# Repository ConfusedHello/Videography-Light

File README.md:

# LUXCRAFT - DIY Film Light

Ever wanted a videography light but died when seeing the insane prices? Me too! This project involves a DIY, high-power RGBW film light built by [@ConfusedHello](https://github.com/confusedhello) and [@Jayx2u](https://github.com/Jayx2u/) for the Hack Club [Highway to Hardware](https://highway.hackclub.com/) program!

We decided to design this project because as students, we honestly don't have the spare cash lying around for one, and we wanted a nice accent light for our planned upcoming videos. It utilises 36 *current controlled* RGBW LEDs running off a 48V supply and controlled with a Xiao RP2040!

For details about the design process or other information, check out the [development journal](https://highway.hackclub.com/projects/ConfusedHello/Videography-Light). A local copy is available in [JOURNAL.md](https://github.com/ConfusedHello/Videography-Light/blob/main/JOURNAL.md).

## The Design
Here's a quick diagram showing how the project works~

And a nice rendered image of the case and control board-

As well as the schematic and PCB for both the control and light boards!

Also the CAD because apparently that's necessary.

## Bill of Materials
Also available in .csv format in [BOM.csv](https://github.com/ConfusedHello/Videography-Light/blob/main/BOM.csv)! BOMs for the PCBs are in [ControlBoard.csv](https://github.com/ConfusedHello/Videography-Light/blob/main/src/Production/Control%20PCB/ControlBoard.csv) and [VideographyLight.csv](https://github.com/ConfusedHello/Videography-Light/blob/main/src/Production/Light%20PCB/VideographyLight.csv)~

|Item                      |Qty.|Price (USD)|Ext. (USD)|Link                                                 |
|--------------------------|----|-----------|----------|-----------------------------------------------------|
|997-L1MCRGB2295MP0        |36  |$1.36      |$48.96    |https://mouser.com/c/?q=997-L1MCRGB2295MP0           |
|81-GRM32EC72A106ME5K      |11  |$0.71      |$7.85     |https://mouser.com/c/?q=81-GRM32EC72A106ME5K         |
|710-7447706101            |11  |$1.01      |$11.11    |https://mouser.com/c/?q=710-7447706101               |
|71-WSLT2010R5000FEA1      |11  |$0.57      |$6.28     |https://mouser.com/c/?q=71-WSLT2010R5000FEA1         |
|625-SS1H10-E3             |11  |$0.28      |$3.11     |https://mouser.com/c/?q=625-SS1H10-E3                |
|621-AL8862SP-13           |11  |$0.54      |$5.93     |https://mouser.com/c/?q=621-AL8862SP-13              |
|179-TB0012-508-04GR       |2   |$1.29      |$2.58     |https://mouser.com/c/?q=179-TB0012-508-04GR          |
|179-TB0012-508-02GR       |2   |$0.69      |$1.38     |https://mouser.com/c/?q=179-TB0012-508-02GR          |
|579-MCP4728-E/UN          |1   |$2.50      |$2.50     |https://mouser.com/c/?q=579-MCP4728-E/UN             |
|713-102010428             |1   |$5.40      |$5.40     |https://mouser.com/c/?q=713-102010428                |
|595-LMR51606XFQDBRQ1      |1   |$2.25      |$2.25     |https://mouser.com/c/?q=595-LMR51606XFQDBRQ1         |
|179-TS046695BK100SMT      |5   |$0.16      |$0.80     |https://mouser.com/c/?q=179-TS046695BK100SMT         |
|71-CRCW12104K70JNAIF      |2   |$0.58      |$1.16     |https://mouser.com/c/?q=71-CRCW12104K70JNAIF         |
|71-CRMA1210AF100KFKF      |1   |$0.85      |$0.85     |https://mouser.com/c/?q=71-CRMA1210AF100KFKF         |
|71-CRCW0402-19.1K-E3      |1   |$0.10      |$0.10     |https://mouser.com/c/?q=71-CRCW0402-19.1K-E3         |
|71-CRCW0402-100K-E3       |1   |$0.10      |$0.10     |https://mouser.com/c/?q=71-CRCW0402-100K-E3          |
|70-IFDC5050JZER470M       |1   |$0.96      |$0.96     |https://mouser.com/c/?q=70-IFDC5050JZER470M          |
|637-1N4148W               |5   |$0.10      |$0.50     |https://mouser.com/c/?q=637-1N4148W                  |
|810-C3225X7R1H106MAC      |2   |$0.96      |$1.92     |https://mouser.com/c/?q=810-C3225X7R1H106MAC         |
|81-GRM155R71C104KA88      |2   |$0.10      |$0.20     |https://mouser.com/c/?q=81-GRM155R71C104KA88         |
|81-GRM188R72A104KA35      |1   |$0.15      |$0.15     |https://mouser.com/c/?q=81-GRM188R72A104KA35         |
|581-KAM32LR72A475KU       |1   |$0.91      |$0.91     |https://mouser.com/c/?q=581-KAM32LR72A475KU          |
|Aluminum Heatsink         |10  |$0.73      |$7.33     |https://www.aliexpress.com/item/4000723868050.html   |
|0.96 Inch OLED Display    |1   |$2.60      |$2.60     |https://www.aliexpress.com/item/1005007614149117.html|
|M2 Heat Insert            |16  |$0.11      |$1.73     |https://www.aliexpress.com/item/1005003582355741.html|
|M2 Screw (10mm)           |16  |$0.21      |$3.40     |https://www.aliexpress.com/item/1005005688616965.html|
|48V Power Supply          |1   |$25.73     |$25.73    |https://www.aliexpress.com/item/1005008528926877.html|
|JLCPCB Control Board      |1   |$2.00      |$2.00     |https://www.jlcpcb.com                               |
|JLCPCB Light Board        |1   |$2.00      |$2.00     |https://www.jlcpcb.com                               |
|JLCPCB Light Board Stencil|1   |$7.00      |$7.00     |https://www.jlcpcb.com                               |
|JLCPCB Shipping           |1   |$21.22     |$21.22    |https://www.jlcpcb.com                               |

**Total:** $178.01 USD

<hr>

Made with ❤️ by [@ConfusedHello](https://github.com/confusedhello) and [@Jayx2u](https://github.com/Jayx2u/)

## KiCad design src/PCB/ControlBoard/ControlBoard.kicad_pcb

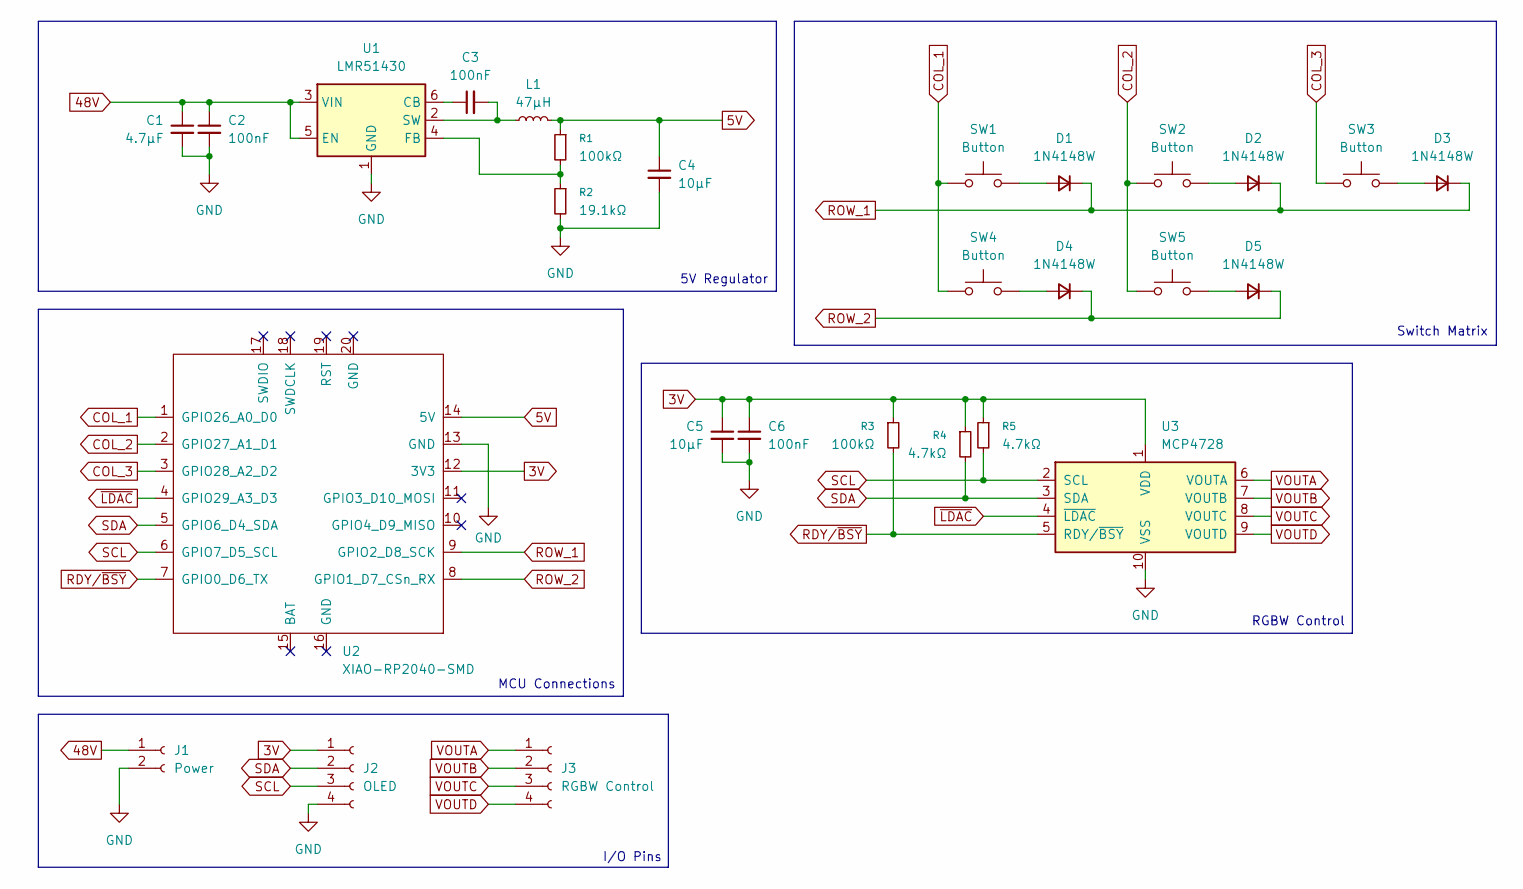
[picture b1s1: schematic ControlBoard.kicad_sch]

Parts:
C1: 4.7μF; C_1210_3225Metric_Pad1.33x2.70mm_HandSolder; Mouser 581-KAM32LR72A475KU
C2: 100nF; C_0603_1608Metric_Pad1.08x0.95mm_HandSolder; Mouser 81-GRM188R72A104KA35
C3, C6: 100nF; C_0402_1005Metric_Pad0.74x0.62mm_HandSolder; Mouser 81-GRM155R71C104KA88
C4, C5: 10μF; C_1210_3225Metric_Pad1.33x2.70mm_HandSolder; Mouser 810-C3225X7R1H106MAC
D1, D2, D3, D4, D5: 1N4148W; D_SOD-123; Mouser 637-1N4148W
J1: Power; TerminalBlock_Phoenix_MKDS-1,5-2-5.08_1x02_P5.08mm_Horizont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; Mouser 179-TB0012-508-02GR
J2: OLED; PinHeader_1x04_P1.00mm_Vertical
J3: RGBW Control; TerminalBlock_Phoenix_MKDS-1,5-4-5.08_1x04_P5.08mm_Horizont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; Mouser 179-TB0012-508-04GR
L1: 47μH; IFDC5050JZER470M; Mouser 70-IFDC5050JZER470M
R1: 100kΩ; R_0402_1005Metric_Pad0.72x0.64mm_HandSolder; Mouser 71-CRCW0402-100K-E3
R2: 19.1kΩ; R_0402_1005Metric_Pad0.72x0.64mm_HandSolder; Mouser 71-CRCW0402-19.1K-E3
R3: 100kΩ; R_1210_3225Metric_Pad1.30x2.65mm_HandSolder; Mouser 71-CRMA1210AF100KFKF
R4, R5: 4.7kΩ; R_1210_3225Metric_Pad1.30x2.65mm_HandSolder; Mouser 71-CRCW12104K70JNAIF
SW1, SW2, SW3, SW4, SW5: Button; TS046695BK100SMT; Mouser 179-TS046695BK100SMT
U1: LMR51430; SOT-23-6; Mouser 595-LMR51606XFQDBRQ1
U2: XIAO-RP2040-SMD; Mouser 713-102010428
U3: MCP4728; MSOP-10_3x3mm_P0.5mm; Mouser 579-MCP4728-E/UN

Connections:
3V: C5.1, C6.1, J2.1, R3.1, R4.1, R5.1, U2.12 (3V3), U3.1 (VDD)
5V: C4.1, L1.2, R1.1, U2.14 (5V)
48V: C1.1, C2.1, J1.1, U1.3 (VIN), U1.5 (EN)
COL_1: SW1.2 (COM_1), SW4.2 (COM_1), U2.1 (GPIO26_A0_D0)
COL_2: SW2.2 (COM_1), SW5.2 (COM_1), U2.2 (GPIO27_A1_D1)
COL_3: SW3.2 (COM_1), U2.3 (GPIO28_A2_D2)
GND: C1.2, C2.2, C4.2, C5.2, C6.2, J1.2, J2.4, R2.2, U1.1 (GND), U2.13 (GND), U3.10 (VSS)
unnamed: D1.2 (A), SW1.4 (COM_2)
unnamed: D2.2 (A), SW2.4 (COM_2)
unnamed: D3.2 (A), SW3.4 (COM_2)
unnamed: D4.2 (A), SW4.4 (COM_2)
unnamed: D5.2 (A), SW5.4 (COM_2)
unnamed: C3.1, U1.6 (CB)
unnamed: R1.2, R2.1, U1.4 (FB)
unnamed: C3.2, L1.1, U1.2 (SW)
RDY/~BSY: R3.2, U2.7 (GPIO0_D6_TX), U3.5 (RDY/~BSY)
ROW_1: D1.1 (K), D2.1 (K), D3.1 (K), U2.9 (GPIO2_D8_SCK)
ROW_2: D4.1 (K), D5.1 (K), U2.8 (GPIO1_D7_CSn_RX)
SCL: J2.3, R5.2, U2.6 (GPIO7_D5_SCL), U3.2 (SCL)
SDA: J2.2, R4.2, U2.5 (GPIO6_D4_SDA), U3.3 (SDA)
VOUTA: J3.1, U3.6 (VOUTA)
VOUTB: J3.2, U3.7 (VOUTB)
VOUTC: J3.3, U3.8 (VOUTC)
VOUTD: J3.4, U3.9 (VOUTD)
~LDAC: U2.4 (GPIO29_A3_D3), U3.4 (~LDAC)

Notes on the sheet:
RGBW Control
5V Regulator
Switch Matrix
MCU Connections
I/O Pins

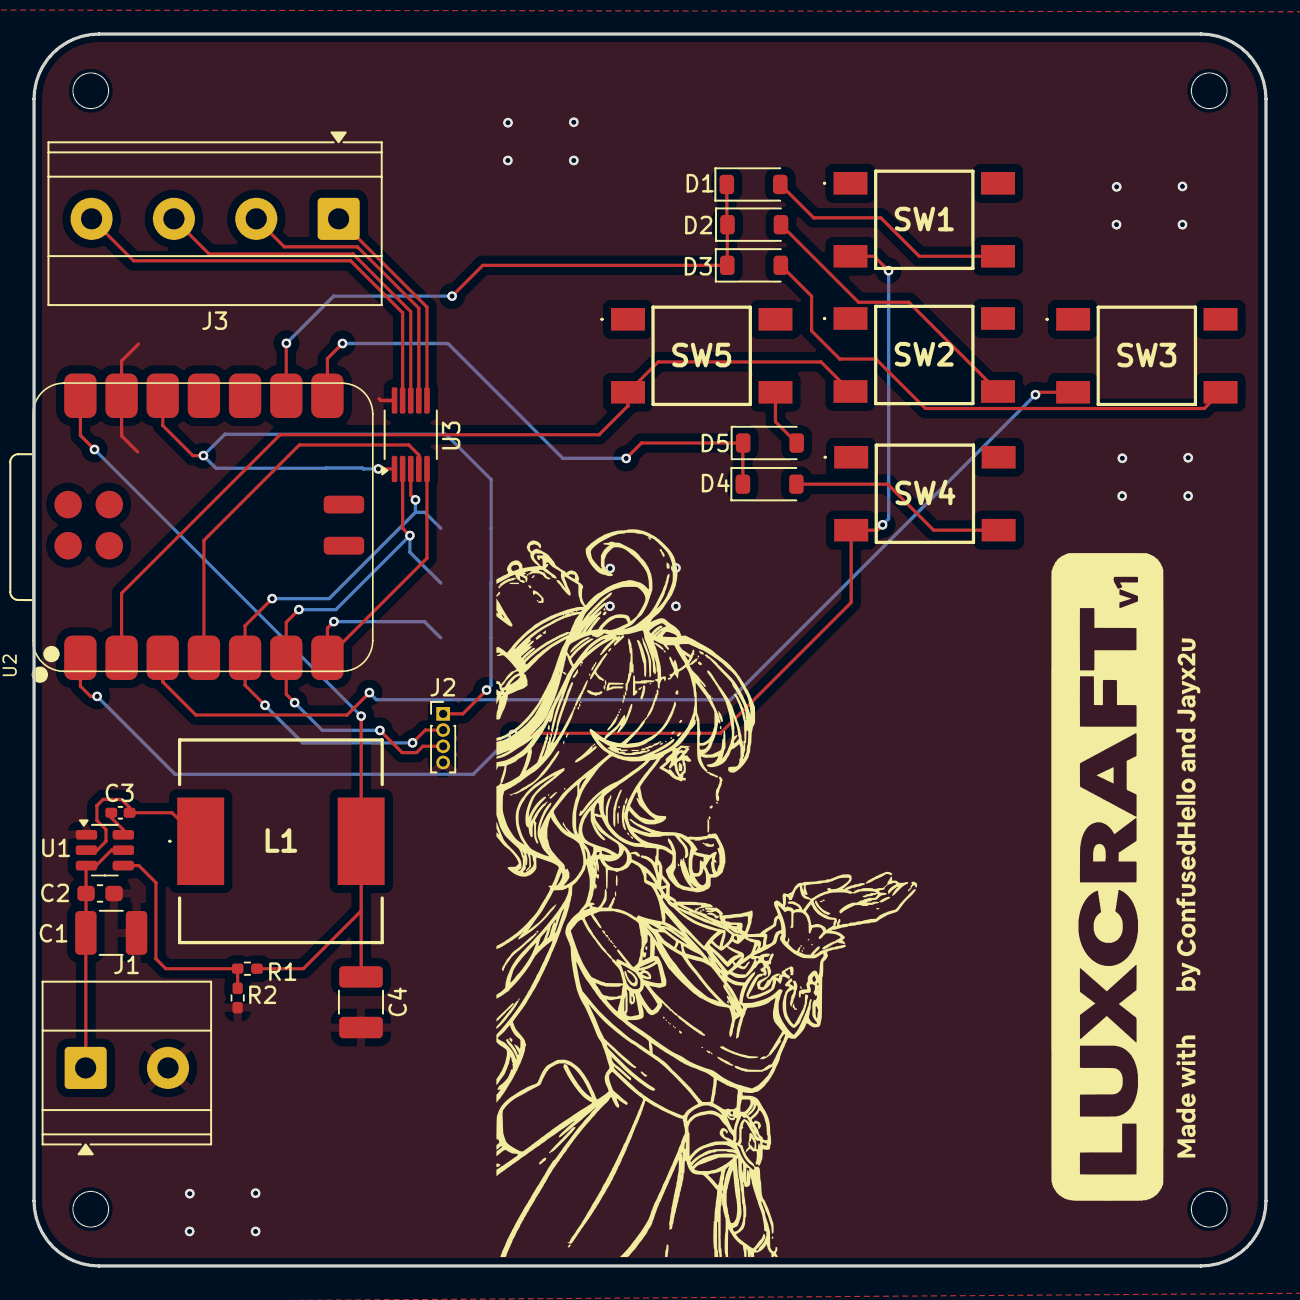
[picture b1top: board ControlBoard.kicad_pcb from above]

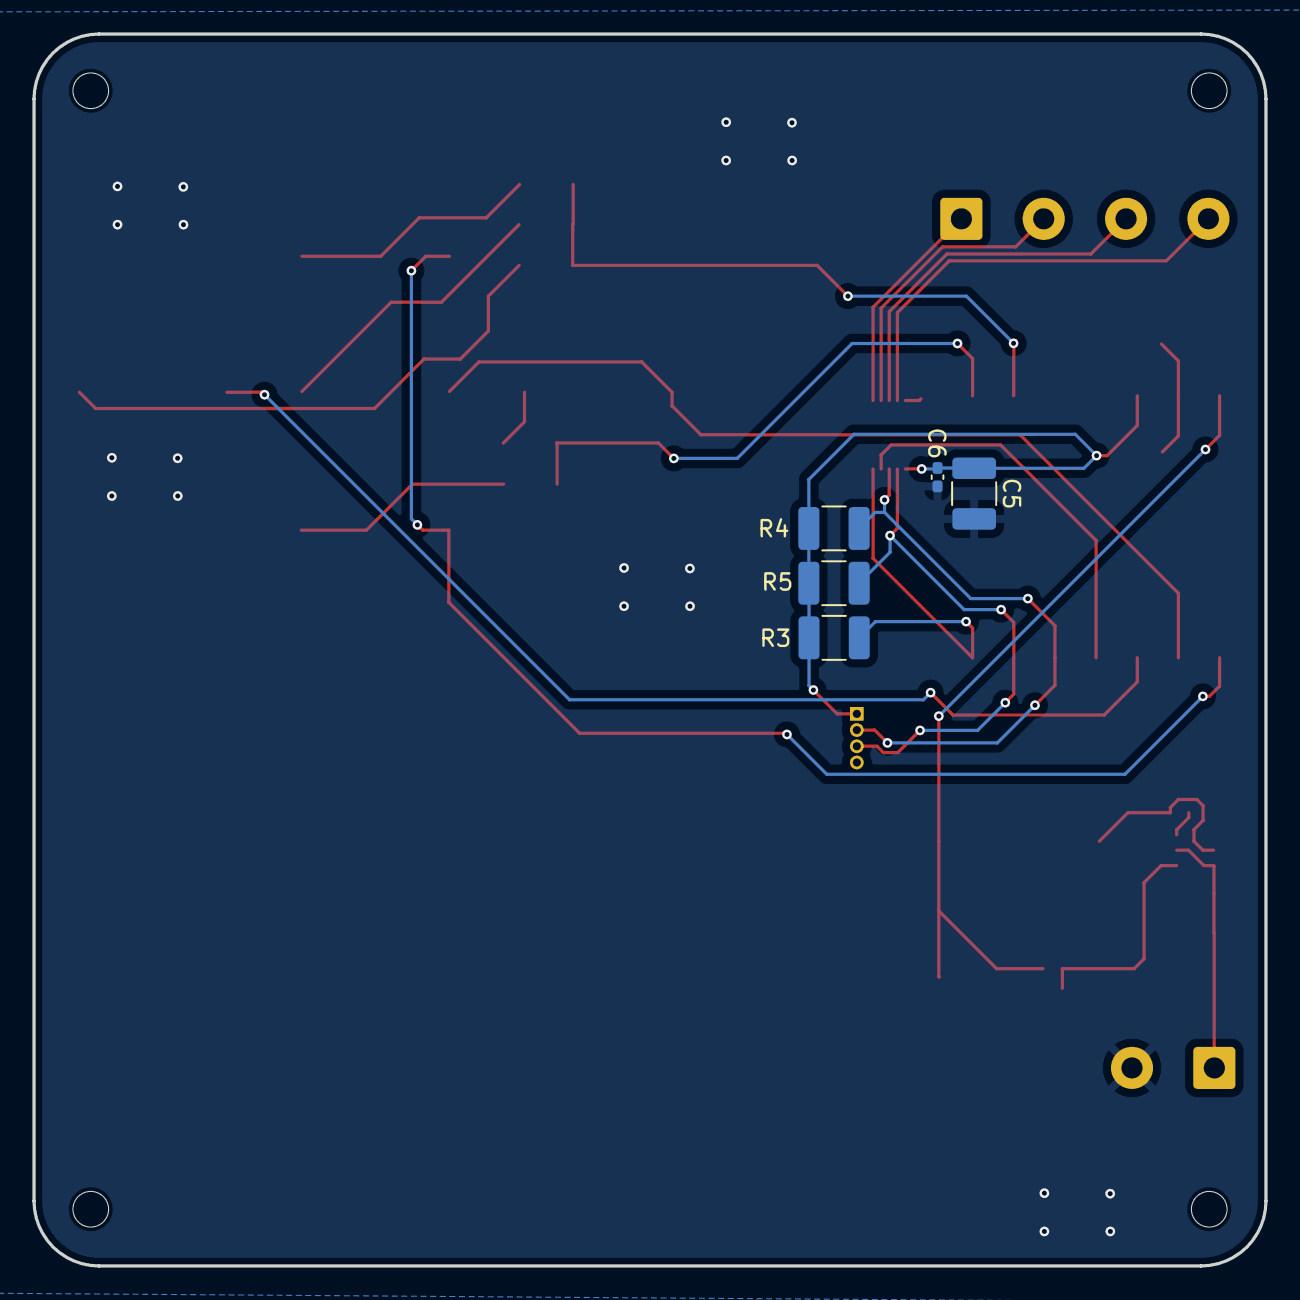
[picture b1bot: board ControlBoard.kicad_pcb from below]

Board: 2 copper layers, 76.0 x 76.0 mm, 28 parts (5 on the bottom side), 25 nets.
